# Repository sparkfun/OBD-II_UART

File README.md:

OBD-II UART
===========

<table class="table table-hover table-striped table-bordered">
  <tr align="center">
   <td></td>
   <td></td>
  </tr>
  <tr align="center">
    <td><a href="https://www.sparkfun.com/products/9555">OBD-II UART (WIG-09555)</a></td>
    <td><a href="https://www.sparkfun.com/products/10769">SparkFun Car Diagnostics Kit (RTL-10769)</a></td>
  </tr>
</table>

A board that provides a serial interface using the ELM327 command set with a vehicle's OBD-II bus, and supports all major OBD-II standards. 

Repository Contents
-------------------
* **/Firmware** - Example Arduino sketch
* **/Hardware** - All Eagle design files (.brd, .sch)
* **/Software** - Information about desktop program to use with this board. 

Documentation
--------------
* **[Hookup Guide](https://learn.sparkfun.com/tutorials/obd-ii-uart-hookup-guide)** - Basic hookup guide for the OBD-II UART.
* **[Getting Started with OBD-II](https://learn.sparkfun.com/tutorials/getting-started-with-obd-ii)** - A general guide to the OBD-II protocols used for communication in automotive and industrial applications.

Product Versions
----------------
* [WIG-09555](https://www.sparkfun.com/products/9555) - OBD-II UART board
* [RTL-10769](https://www.sparkfun.com/products/10769) - Car Diagnostics Kit Retail, with OBD-II UART and OBD to DB9 cable.

License Information
-------------------
The hardware is released under [Creative Commons Share-alike 3.0](http://creativecommons.org/licenses/by-sa/3.0/).  
All other code is open source so please feel free to do anything you want with it; you buy me a beer if you use this and we meet someday ([Beerware license](http://en.wikipedia.org/wiki/Beerware)).

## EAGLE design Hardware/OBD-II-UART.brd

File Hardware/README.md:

# What Are these Files?

The .sch and .brd files hare are Eagle CAD schematic and PCB design files.
These files were created with Eagle 6.4.0, you'll need Eagle 6.0 or later to open them up. There is a free, lite, version of Eagle available from [cadsoftusa.com](cadsoftusa.com).

# License

This product is open source! These Eagle files are released under the Creative Commons Share-Alike Attribution license ([CC BY-SA 3.0](http://creativecommons.org/licenses/by-sa/3.0/us/)).

Please use, reuse, and modify these files as you see fit. Please maintain attribution and release anything derivative under the same license.

- Your friends at SparkFun.

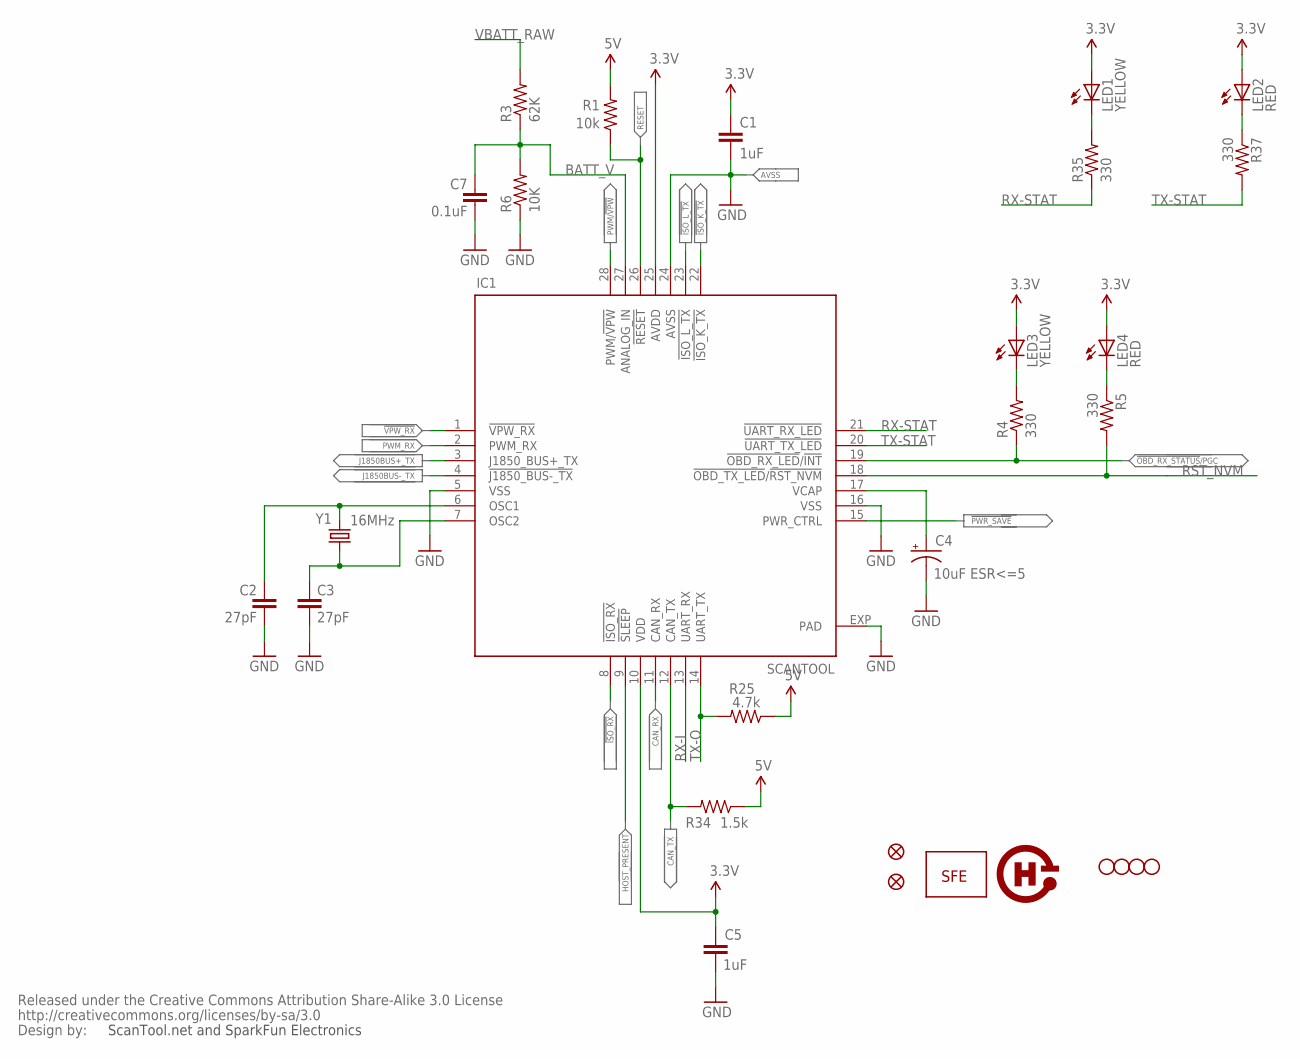
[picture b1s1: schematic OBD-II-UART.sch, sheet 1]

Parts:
C1, C5: 1uF; 0402-CAP
C2, C3: 27pF; 0402-CAP
C4: 10uF ESR<=5; EIA3216
C7: 0.1uF; 0402-CAP
IC1: SCANTOOL; _STN_SCANTOOL_QFN-28-S
JP2, JP10: FIDUCIAL1X2; FIDUCIAL-1X2
JP3: LOGO-SFENEW; SFE-NEW-WEBLOGO
JP4, JP5, JP6, JP7: STAND-OFF
LED1, LED3: YELLOW; LED-0603
LED2, LED4: RED; LED-0603
R1: 10k; 0402-RES
R3: 62K; 0402-RES
R4, R5, R35, R37: 330; 0402-RES
R6: 10K; 0402-RES
R25: 4.7k; 0402-RES
R34: 1.5k; 0402-RES
U$1: CREATIVE_COMMONS
U$14: OSHW-LOGO
Y1: 16MHz; CRYSTAL-SMD-5X3

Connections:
3.3V: C1.1, C5.1, IC1.10 (VDD), IC1.25 (AVDD), LED1.A, LED2.A, LED3.A, LED4.A; also elsewhere on the board
5V: R1.2, R25.1, R34.1; also elsewhere on the board
!ISO_K_TX: IC1.22 (!ISO_K_TX); also elsewhere on the board
!ISO_L_TX: IC1.23 (!ISO_L_TX); also elsewhere on the board
!ISO_RX: IC1.8 (!ISO_RX); also elsewhere on the board
!OBD_RX_STATUS!/PGC: IC1.19 (!OBD_RX_LED!/!INT), R4.1
!PWR_SAVE: IC1.15 (PWR_CTRL)
!VPW_RX: IC1.1 (!VPW_RX); also elsewhere on the board
BATT_V: C7.1, IC1.27 (ANALOG_IN), R3.1, R6.2
CAN_RX: IC1.11 (CAN_RX); also elsewhere on the board
CAN_TX: IC1.12 (CAN_TX), R34.2; also elsewhere on the board
GND: C1.2, C2.2, C3.2, C4.C (-), C5.2, C7.2, IC1.5 (VSS), IC1.16 (VSS), IC1.24 (AVSS), IC1.EXP (PAD), R6.1; also elsewhere on the board
HOST_PRESENT: IC1.9 (!SLEEP)
J1850BUS+_TX: IC1.3 (J1850_BUS+_TX); also elsewhere on the board
J1850BUS-_TX: IC1.4 (!J1850_BUS-_TX); also elsewhere on the board
unnamed: C4.A (+), IC1.17 (VCAP)
unnamed: LED3.C, R4.2
unnamed: LED4.C, R5.1
unnamed: LED1.C, R35.2
unnamed: LED2.C, R37.1
OSC1: C2.1, IC1.6 (OSC1), Y1.3 (2)
OSC2: C3.1, IC1.7 (OSC2), Y1.1
PWM/!VPW: IC1.28 (PWM/!VPW); also elsewhere on the board
PWM_RX: IC1.2 (PWM_RX); also elsewhere on the board
RESET: IC1.26 (!RESET), R1.1
RST_NVM: IC1.18 (!OBD_TX_LED!/!RST_NVM), R5.2; also elsewhere on the board
RX-I: IC1.13 (UART_RX); also elsewhere on the board
RX-STAT: IC1.21 (!UART_RX_LED), R35.1
TX-O: IC1.14 (UART_TX), R25.2; also elsewhere on the board
TX-STAT: IC1.20 (!UART_TX_LED), R37.2
VBATT_RAW: R3.2; also elsewhere on the board

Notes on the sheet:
AVSS
ScanTool.net and SparkFun Electronics

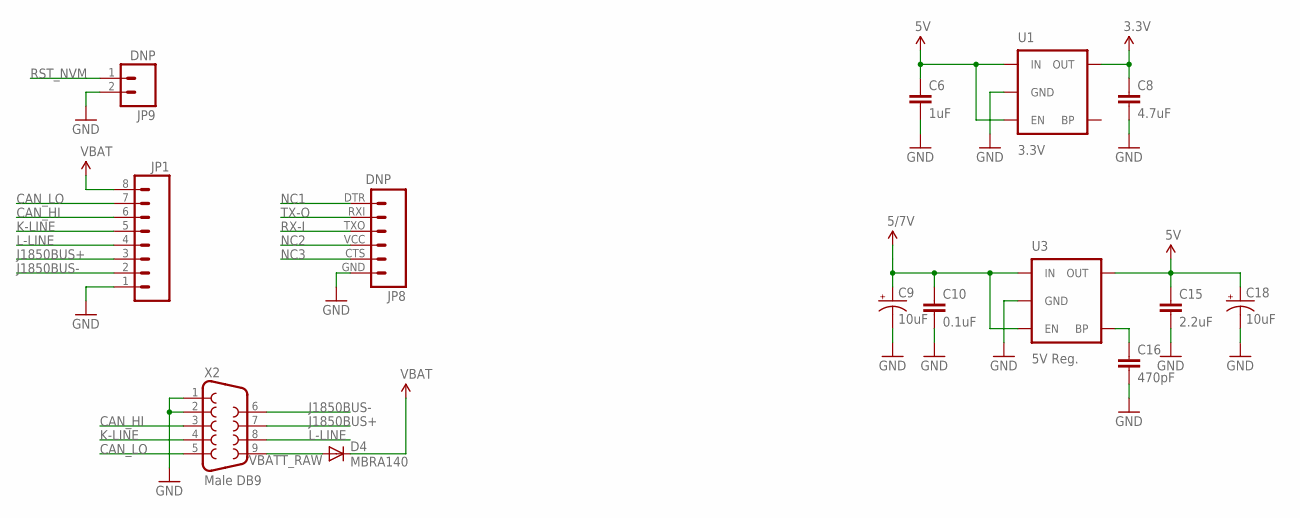
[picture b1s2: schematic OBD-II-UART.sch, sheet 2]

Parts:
C6: 1uF; 0402-CAP
C8: 4.7uF; 0402-CAP
C9, C18: 10uF; EIA3216
C10: 0.1uF; 0402-CAP
C15: 2.2uF; 0402-CAP
C16: 470pF; 0402-CAP
D4: MBRA140; SMA-DIODE
JP1: M08; 1X08
JP8: DNP; FTDI_BASIC
JP9: DNP; 1X02
U1: 3.3V; SOT23-5
U3: 5V Reg.; SOT23-5
X2: Male DB9; DB9_MALE

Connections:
3.3V: C8.1, U1.5 (OUT); also elsewhere on the board
5V: C6.1, C15.1, C18.A (+), U1.1 (IN), U1.3 (EN), U3.5 (OUT); also elsewhere on the board
CAN_HI: JP1.6, X2.3; also elsewhere on the board
CAN_LO: JP1.7, X2.5; also elsewhere on the board
GND: C6.2, C8.2, C9.C (-), C10.2, C15.2, C16.2, C18.C (-), JP1.1, JP8.GND (6), JP9.2, U1.2 (GND), U3.2 (GND), X2.1, X2.2; also elsewhere on the board
J1850BUS+: JP1.3, X2.7; also elsewhere on the board
J1850BUS-: JP1.2, X2.6; also elsewhere on the board
K-LINE: JP1.5, X2.4; also elsewhere on the board
L-LINE: JP1.4, X2.8; also elsewhere on the board
unnamed: C16.1, U3.4 (BP)
NC1: JP8.DTR (1)
NC2: JP8.VCC (4)
NC3: JP8.CTS (5)
RST_NVM: JP9.1; also elsewhere on the board
RX-I: JP8.TXO (3); also elsewhere on the board
TX-O: JP8.RXI (2); also elsewhere on the board
VBAT: D4.C, JP1.8; also elsewhere on the board
VBATT_RAW: D4.A, X2.9; also elsewhere on the board
VCC: C9.A (+), C10.1, U3.1 (IN), U3.3 (EN); also elsewhere on the board

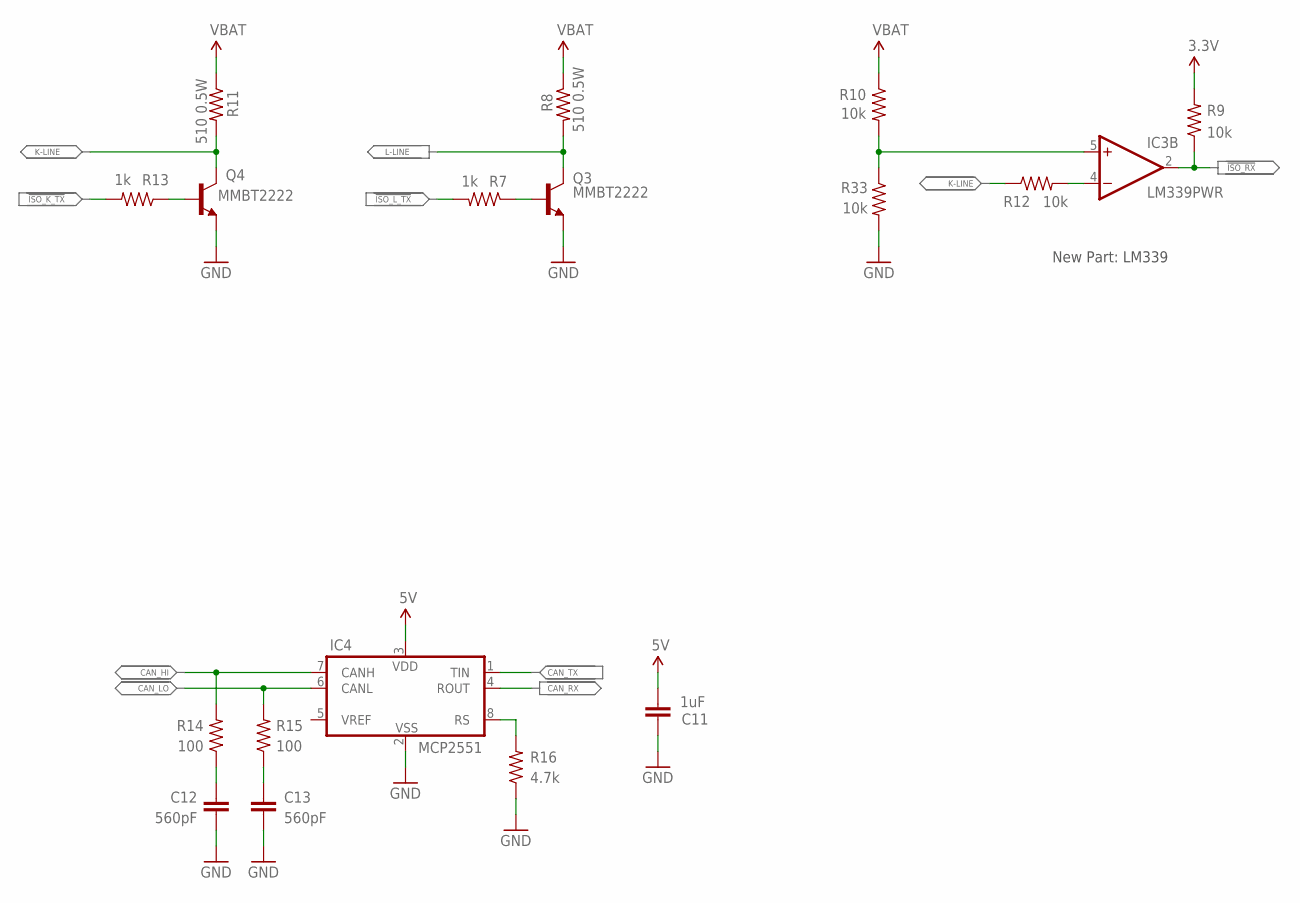
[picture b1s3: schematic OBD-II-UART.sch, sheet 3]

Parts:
C11: 1uF; 0402-CAP
C12, C13: 560pF; 0402-CAP
IC3: LM339PWR; TSSOP-14
IC4: MCP2551; SO-8
Q3, Q4: MMBT2222; SOT23-3
R7, R13: 1k; 0402-RES
R8, R11: 510 0.5W; 2010
R9, R10, R12, R33: 10k; 0402-RES
R14, R15: 100; 0402-RES
R16: 4.7k; 0402-RES

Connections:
3.3V: R9.2; also elsewhere on the board
5V: C11.1, IC4.3 (VDD); also elsewhere on the board
!ISO_K_TX: R13.2; also elsewhere on the board
!ISO_L_TX: R7.2; also elsewhere on the board
!ISO_RX: IC3.2 (OUT), R9.1; also elsewhere on the board
CAN_HI: IC4.7 (CANH), R14.2; also elsewhere on the board
CAN_LO: IC4.6 (CANL), R15.2; also elsewhere on the board
CAN_RX: IC4.4 (ROUT); also elsewhere on the board
CAN_TX: IC4.1 (TIN); also elsewhere on the board
GND: C11.2, C12.2, C13.2, IC4.2 (VSS), Q3.2 (E), Q4.2 (E), R16.1, R33.2; also elsewhere on the board
K-LINE: Q4.3 (C), R11.2, R12.1; also elsewhere on the board
L-LINE: Q3.3 (C), R8.2; also elsewhere on the board
unnamed: Q4.1 (B), R13.1
unnamed: Q3.1 (B), R7.1
unnamed: IC3.5 (+IN), R10.2, R33.1
unnamed: C12.1, R14.1
unnamed: IC4.8 (RS), R16.2
unnamed: IC3.4 (-IN), R12.2
unnamed: C13.1, R15.1
VBAT: R8.1, R10.1, R11.1; also elsewhere on the board

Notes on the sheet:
New Part: LM339

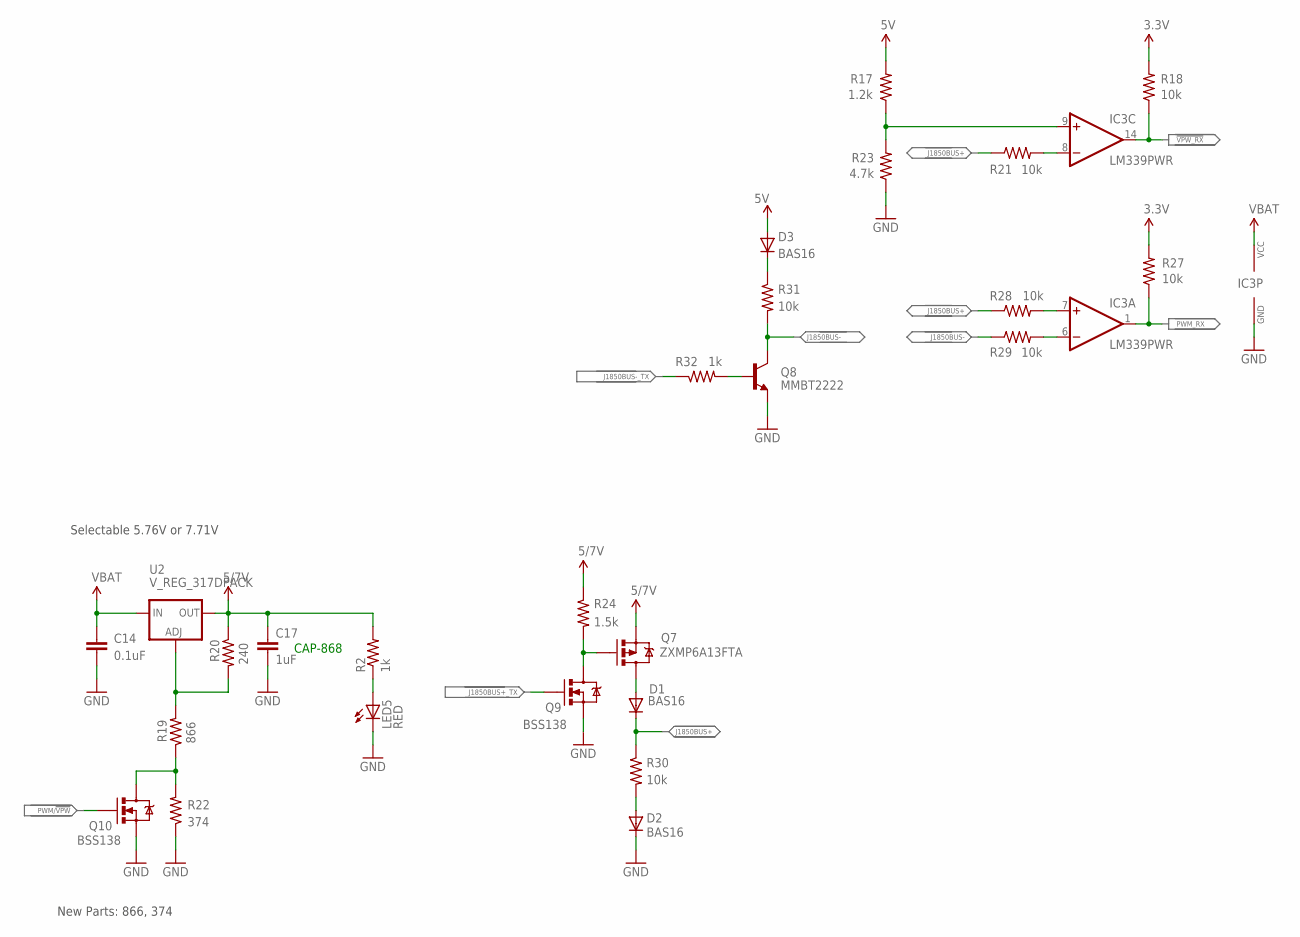
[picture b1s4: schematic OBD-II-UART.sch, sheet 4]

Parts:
C14: 0.1uF; 0402-CAP
C17: 1uF; 0402-CAP
D1, D2, D3: BAS16; SOD-323
IC3: LM339PWR; TSSOP-14
LED5: RED; LED-0603
Q7: ZXMP6A13FTA; SOT23
Q8: MMBT2222; SOT23-3
Q9, Q10: BSS138; SOT23-3
R2, R32: 1k; 0402-RES
R17: 1.2k; 0402-RES
R18, R21, R27, R28, R29, R30, R31: 10k; 0402-RES
R19: 866; 0402-RES
R20: 240; 0402-RES
R22: 374; 0402-RES
R23: 4.7k; 0402-RES
R24: 1.5k; 0402-RES
U2: V_REG_317DPACK; V-REG_DPACK

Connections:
3.3V: R18.2, R27.2; also elsewhere on the board
5V: D3.2 (A), R17.2; also elsewhere on the board
!VPW_RX: IC3.14 (OUT), R18.1; also elsewhere on the board
GND: C14.2, C17.2, D2.1 (C), IC3.12 (GND), LED5.C, Q8.2 (E), Q9.2 (S), Q10.2 (S), R22.1, R23.1; also elsewhere on the board
J1850BUS+: D1.1 (C), R21.1, R28.1, R30.1; also elsewhere on the board
J1850BUS+_TX: Q9.1 (G); also elsewhere on the board
J1850BUS-: Q8.3 (C), R29.1, R31.2; also elsewhere on the board
J1850BUS-_TX: R32.1; also elsewhere on the board
unnamed: IC3.7 (+IN), R28.2
unnamed: IC3.6 (-IN), R29.2
unnamed: IC3.8 (-IN), R21.2
unnamed: R19.2, R20.2, U2.1 (ADJ)
unnamed: D1.2 (A), Q7.3 (D)
unnamed: IC3.9 (+IN), R17.1, R23.2
unnamed: D3.1 (C), R31.1
unnamed: Q7.1 (G), Q9.3 (D), R24.2
unnamed: Q10.3 (D), R19.1, R22.2
unnamed: D2.2 (A), R30.2
unnamed: Q8.1 (B), R32.2
unnamed: LED5.A, R2.1
PWM/!VPW: Q10.1 (G); also elsewhere on the board
PWM_RX: IC3.1 (OUT), R27.1; also elsewhere on the board
VBAT: C14.1, IC3.3 (VCC), U2.3 (IN); also elsewhere on the board
VCC: C17.1, Q7.2 (S), R2.2, R20.1, R24.1, U2.4 (OUT); also elsewhere on the board

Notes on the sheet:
Selectable 5.76V or 7.71V
New Parts: 866, 374
CAP-868

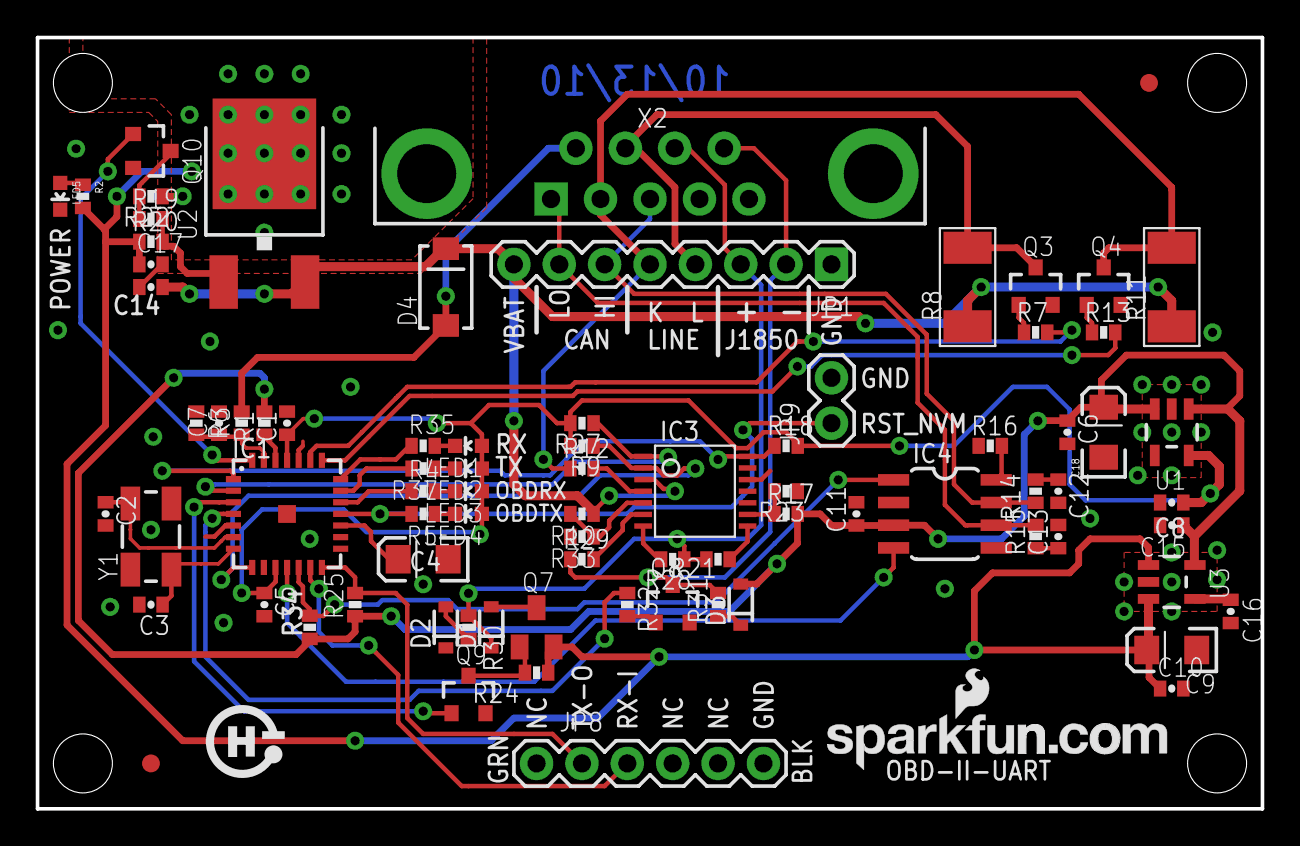
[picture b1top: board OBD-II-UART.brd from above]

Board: 2 copper layers, 68.6 x 43.2 mm, 88 parts (0 on the bottom side), 57 nets.

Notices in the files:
parts and their libraries:
SparkFun: Released under the Creative Commons Attribution Share-Alike 3.0 License
SparkFun-Aesthetics: Licensing: CC v3.0 Share-Alike You are welcome to use this library for commercial purposes.
